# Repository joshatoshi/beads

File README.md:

# Mutable Instruments Beads Pedalboard Skiff, Stereo Audio/MIDI-to-CV Bridge & Autonomous Drift Workstation

A complete, fabrication-ready **low-profile guitar pedalboard skiff (`152.0 × 185.6 × 45.0 mm`, Bambu Lab X2D `PETG-HF`)** that houses an unmodified **Mutable Instruments Beads (`14 HP × 3U`)** Eurorack granular synthesizer directly on a standard **`9V–18V DC` center-negative guitar pedalboard**, pairing it with a **popless PhotoMOS + Omron relay stereo `1/4"` guitar interface**, **hardware `MIDI THRU` + `USB-C` MIDI**, and an **8-channel `-8.2V..+8.2V` `RP2040` Cubic Bezier "Drift" & calibrated `1V/Oct` CV workstation**.

---

## Visual Architecture & Mechanical Views

| North-Wall Pedalboard I/O | True Mechanical Y–Z Cross-Section |
|---|---|
|  |  |

| Exploded Multi-Board Architecture | Off-Board Wiring & Polarity Checklist |
|---|---|
|  |  |

---

## Key Engineering Highlights

1. **Multi-Stage Protected `9V–18V DC` Center-Negative → Ultra-Quiet `±12.0V` Eurorack Power (`plan/01`):**
   - Standard **`2.1 × 5.5 mm` Center-Negative** input (`Outer Sleeve = +9..18V`, `Center Pin = 0V GND`) via an all-insulated LCP panel DC jack (**Tensility `54-00401`**) into a **`33V 1.1A` resettable PTC (`SMD1812B110TF/33`, `C269134`)**, **`600W` bidirectional TVS (`SMBJ20CA`, `C19077576`)**, **`AO3401A` reverse-polarity P-MOSFET** with **`18V`-safe `9.1V` Zener gate clamp (`BZX84-C9V1`)**, and input LC Pi-filter (`BLM18PG121SN1D` `2A` ferrite).
   - **`TPS5430DDAR` (`+5.08V @ 500 kHz`, TI `SLVS632L` §7.2.3 RC-compensated: `PM = +87.3°` nominal / `+68.2°` derated, `GM = +20.5 / +15.3 dB`, `164.1 µF` output bank)** → **`TPS65131RGER` (`+14.65V / -14.56V @ 1.38 MHz` fixed-PWM, `PSP/PSN=GND`)** → linear **`LM317AG-TN3-R` (`+12.0V_EUR`)** & ESR-damped **`79M12(TP)` (`-12.0V_EUR`)** post-regulators + `2A` ferrite LC filters feeding the shrouded **`2×5` Eurorack IDC box header (`J_EURO_PWR`)** marked **`RED STRIPE / -12V (PINS 1-2)`**.
   - **`< 1 µA` Bidirectional `USB-C VBUS` ↔ `+5V_BUCK` Isolation, Glitch-Free USB 2.0 Suspend & `3.3V → 5V` Level Shifting:** `D_OR_PED` (`1N5819WS`) + `D_ESD_VP` (`1N4148W`) + `C100` (`100 nF`) reverse-isolated `SRV05-4` `ESD_VP` clamp + `PIN_VBUS_DET`-gated `RP2040` `1.5 kΩ` D+ pull-up (`< 3 nA` zero back-feed into powered-off hosts and immediate `< 16 mV` hot-unplug `VBUS_DET` drop with zero `SUSPENDED` `SE0` glitches!) + `I_off`-isolated **`SN74AHCT541PWR`** (`C50989`) SPI/CS level shifter with `+5V_BUCK` pull-ups (`R77..R80`), ensuring `MCP4822` `V_IH >= 3.56V` compliance during simultaneous `USB-C` + pedal DC or USB-only UF2 bench flashing.

2. **Stereo `1/4"` Guitar ↔ Eurorack Gain Staging & Boutique Popless PhotoMOS True Bypass (`plan/02`):**
   - `4×` North-edge PCB-mounted **Neutrik `NMJ4HCD2`** `1/4"` jacks (`OUT R`, `OUT L/Mono`, `IN R` passively normalled from `IN L/Mono` via `TN`; output `TN` pins strictly isolated — **zero flying audio wires!**).
   - **`1 MΩ` `TL072CDT` JFET Stereo Guitar Preamp** (`+18.0 dB` at `12 o'clock` on dual-gang `IN TRIM` → `SEND L / SEND R` Thonkiconn) paired with **`100 kΩ` `NE5532DR` + `TL072CDT` Stereo Return** (`-18.0 dB` at `12 o'clock` on dual-gang `OUT TRIM` ← `RET L / RET R` Thonkiconn) = **`0.0 dB` end-to-end unity gain and `0°` non-inverting phase**.
   - **Clickless / Popless Relay True Bypass (`15.0 ms` Window + `250 ms` POR Blanking):** Combines `2× Omron G6K-2F-Y-TR DC5` gold-clad DPDT relays (`fail-safe passive copper bypass when unpowered`) with **`2× Toshiba TLP172AM` (`SOP-4`, `3.75 kV` optical isolation, `0 pC` charge injection) PhotoMOS shunt mutes** (`47.3 dB` mute attenuation, `< 1.6 mV` bounce transient), `8× 2.2 MΩ` zero-DC bleed resistors, soft-slewed coil/LED drive, and **EQD Flexi-Switch auto-momentary** (`short tap < 350 ms` toggles; `hold >= 350 ms` momentarily engages Beads while held).
   - **Overvoltage-Proof Guitar Peak & Pluck Detector:** `+3.30V`-powered **`MCP6002T-I/SN`** + `BAV99` clamp (`<= 2.79V` even under `12 Vpk` fault surges) feeding `RP2040 ADC0`.

3. **8× Universal `-8.2V..+8.2V` Bipolar CV / Calibrated `1V/Oct` / Gate Outputs + Hardware `MIDI THRU` (`plan/02`, `plan/05`):**
   - `4× MCP4822-E/SN` (`12-bit` Dual SPI DACs, internal `2.048V` ref, `0xFFFF` delta-gated SPI) + `CJ431`/`OP07CDR` `+2.495V` precision offset reference + `4× TL072CDT` bipolar drivers + `1 kΩ` protection resistors → `8×` `WQP-PJ398SM` Thonkiconn jacks (`CV 1..CV 8`).
   - Top-mounted `3.5 mm` TRS `MIDI IN` with right-angle **C&K `JS202011AQN` `MIDI TYPE A / B`** crossover switch → **`H11L1M` (`DIP-6`)** optocoupler → **`74HC14D` zero-latency hardware `MIDI THRU`** (`3.5 mm` TRS Type A) + `RP2040 UART0_RX` merged seamlessly with **`USB-C` MIDI**.
   - Per-channel **Autonomous `C¹` Cubic Bezier Random Drift**, free/clock-synced **256-pt LFOs** (`Sine`, `Tri`, `Ramp Up/Down` for `TIME` scrubbing, `Square`, `Slewed S&H`), **Euclidean `(Steps, Hits)` Triggers**, **9-Octave LUT-Calibrated `1V/Oct` Pitch CV**, **MIDI Gate/Trig/Clock-Div/CC**, **Guitar Envelope/Pluck**, and **FS2 `FREEZE` / `SEED` Tap-Tempo** — viewed on a **`0.96"` `128×64` `SSD1306` OLED oscilloscope** and stored in **dual-slot A/B `CRC32` + `write_seq` QSPI Flash (`32` presets)**.

4. **Cost-Optimized 3-Board 2-Layer JLCPCB Partitioning & Bambu Lab X2D `PETG-HF` Stepped Enclosure (`plan/03`, `plan/04`):**
   - **`main_board` (`142.0 × 146.6 mm`, 2-layer `1.6 mm` FR4):** Single-sided Top-Side JLCPCB SMT PCBA (`77` unique verified LCSC parts: **`54` Basic, `7` Preferred, `16` Extended**, `314` SMD placements, `0` THT in CPL, **`92.46%` single largest connected `B.Cu` ground island** with `0` un-stitched islands, `0.80 × 1.60 mm` `SJ1-3523N` plated slots, `0.500 mm` min NPTH edge web + `0.70 mm` `SJ1-3523N` collar relief notches, `203` PCB nets, `ERC = 0/0`, `DRC = 0` errors / `0` warnings, `unconnected = 0`).
   - **`ui_mezzanine` (`68.0 × 108.0 mm`, 2-layer `1.6 mm` FR4, `$0` PCBA fee):** Pure user-hand-soldered THT carrier (`12×` Thonkiconn, `SSD1306` w/ reversible `JP_OLED_PWR` & `8.13 mm <= 8.50 mm` low-profile `DW-04-07-T-S-200` stack, `EC11E15244G1` 15 PPR bushingless, `BACK`, `2×` vertical dual-gang `10 kΩ` trim pots `Alpha RD902F-40-15R1-B10K-00D`, `PEAK` LED, `B.Cu`-mounted `0.0000 mm` XY-matched `2×8` BTB sockets, `21/21` local `${KIPRJMOD}` 3D STEP links).
   - **`faceplate_14hp` (`70.80 × 128.50 mm`, 2-layer `1.6 mm` Matte-Black FR4, `$0` PCBA fee):** Sits on the `-1.60 mm` Left 3U rail shelf alongside Mutable Instruments Beads on the `-2.00 mm` Right 3U rail shelf — **both panels dead-flush at `Z = 0.00 mm`** above a `-12.00 mm` stepped front stomp apron (`92.0 mm` footswitch spacing) reinforced by `4×` full-height internal stomp pillars and `18×` `M3` brass heat-set inserts (**`0.000 mm³` pairwise `OCP BRepAlgoAPI_Common` collision across all `427` un-grouped solids + `0.000 mm³` `15`-pose × `331`-part rigid-body insertion sweep**).

---

## Repository Structure

```text
├── PLAN.md                           # Master specification index
├── README.md                         # Project overview, flashing & verification guide
├── hardware_contract.json            # Single-source-of-truth spatial, PCB & GPIO contract
├── plan/                             # Authoritative 00..05 engineering specifications
├── hardware/
│   ├── main_board/                   # KiCad 9 2-layer Main Floor PCB + hierarchical schematics
│   ├── ui_mezzanine/                 # KiCad 9 2-layer 14HP THT Mezzanine PCB
│   ├── faceplate_14hp/               # KiCad 9 14HP Matte-Black FR4 Eurorack Panel
│   ├── beads_custom.kicad_sym        # Project-local ERC-typed custom schematic symbols
│   ├── beads_custom.pretty/          # Project-local custom footprints (${KIPRJMOD}-portable)
│   ├── beads_custom.3dshapes/        # Local parametric 3D STEP component models
│   └── spice/verify_analog.py        # Netlist-derived 8-gate ngspice verification suite
├── manufacturing/
│   ├── main_board/                   # Gerbers, Drills, Schematic PDF, JLCPCB SMT BOM & CPL
│   ├── ui_mezzanine/                 # Gerbers, Drills, Schematic PDF & THT BOM
│   ├── faceplate_14hp/               # Gerbers, Drills & Schematic PDF (Matte Black FR4)
│   └── HAND_SOLDER_AND_BOM.md        # Complete JLCPCB order settings, DigiKey/Thonk BOM & build guide
├── firmware/
│   ├── Makefile & CMakeLists.txt     # Bare-metal ARM UF2 build + Pico SDK CMake + Host unit tests
│   ├── include/ & src/               # Dual-core RP2040 C11 engine, Bezier/LFO/1V-Oct, OLED, Presets
│   ├── target/                       # RP2040 XIP boot2, linker script & silicon register HAL
│   ├── tests/test_beads_firmware.c   # 12 deterministic host silicon-mock assert() test suites
│   └── build/beads_bridge.uf2        # Ready-to-flash RP2040 UF2 firmware image (0xE48BFF56)
├── cad/
│   ├── build_enclosure.py            # Parametric Build123d enclosure, 427-solid assembly & studio renderer
│   ├── verify_3d_collisions.py       # 427-solid pairwise + 331-part kinematic OCP BRepAlgoAPI_Common 0.000 mm³ gate
│   └── exports/                      # Print-ready STLs, STEPs, Studio PNGs & Wiring Diagram
└── scripts/
    ├── generate_3d_shapes.py         # Deterministic STEP builder for hardware/beads_custom.3dshapes
    ├── layout_boards.py              # Deterministic KiCad 9 board placement & outline generator
    ├── route_boards.py               # Specctra DSN + bounded Freerouting + fresh-process zone filler
    ├── verify_pcb_gates.py           # Gate 1 KiCad 9 ERC/DRC/Pour/BTB/Paste/Keepout verifier
    ├── export_manufacturing.py       # Gate 2 Gerber/BOM/CPL exporter & jlcpcb_parts.db verifier
    └── run_all_checks.sh             # Master 5-gate end-to-end verification suite
```

---

## Headerless USB-C UF2 Firmware Flashing (`Zero SWD Pins Required`)

1. **First-Time Factory Bring-Up:**
   - Plug a `USB-C` cable from your computer into the North-wall `USB-C` port (with or without `9–18V` pedal power connected — `< 1 µA` isolated!).
   - A fresh `RP2040` automatically enumerates as **`RPI-RP2`** USB Mass Storage. Copy `firmware/build/beads_bridge.uf2` directly onto the `RPI-RP2` drive.
2. **In-Case Field Updates (No Disassembly Needed):**
   - **Via Front-Panel OLED:** Press `BACK` from the Scope view to enter **`SYSTEM MENU`**, scroll to **`USB FW UPDATE`**, and click the encoder — the skiff reboots immediately into `RPI-RP2` UF2 mode.
   - **Via `1200-baud` USB-CDC Touch:** Run `picotool load -f firmware/build/beads_bridge.uf2` (or open/close the virtual serial port at `1200 bps`).
   - **Hardware Fallback:** Hold onboard SMD **`BOOTSEL` (`SW_BOOT`)** while plugging in `USB-C`.

---

## Bambu Lab X2D `PETG-HF` 3D Printing Guide

- **Print Files:** `cad/exports/beads_enclosure_shell.stl` (`152.0 × 185.6 × 45.0 mm`) and `cad/exports/beads_bottom_lid.stl` (`147.1 × 180.7 × 5.0 mm`).
- **Recommended Bambu Studio Settings (`Bambu Lab X2D`):**
  - **Nozzle 1 (Structural Body):** **Bambu `PETG-HF`** (Charcoal / Black), `0.4 mm` hardened steel nozzle, `0.20 mm` layer height, **`4` wall loops**, `5` top / `5` bottom shell layers, **`25%` Gyroid infill**.
  - **Nozzle 2 (Dedicated Support Interface):** **`Support for PLA/PETG`** (or soluble breakaway interface), `0 mm` top Z-distance, `2` interface layers under the 3U Eurorack rail lips and stepped front stomp apron ceiling for glass-flat overhang surfaces.
  - **Orientation:** Place `beads_enclosure_shell.stl` **flat upright (`Z = -45.0 mm` outer skirt on textured PEI plate)** and `beads_bottom_lid.stl` **outer bottom face (`Z = -45.0 mm`) down on textured PEI plate**.
- Full hand-soldering, `18× M3` heat-set insert installation, `JP_OLED_PWR` jumper selection, and step-by-step wiring instructions are in **[`manufacturing/HAND_SOLDER_AND_BOM.md`](manufacturing/HAND_SOLDER_AND_BOM.md)**.

---

## Reproducing All 5 Verification Gates End-to-End

```bash
bash scripts/run_all_checks.sh
```

`scripts/run_all_checks.sh` executes all 5 mandatory engineering gates from scratch and exits `0`:
1. **Gate 1 (`scripts/verify_pcb_gates.py`):** KiCad 9 `ERC = 0/0`, `DRC = 0` errors / `0` warnings, `unconnected = 0` across all 3 boards, `${KIPRJMOD}` portability + `21/21` `ui_mezzanine` & `SW_MIDI_AB` local STEPs, `92.46%` single largest connected `B.Cu` GND island (`>= 88%`, `0` un-stitched islands), `>= 0.50 mm` bulk power trunks, `0.500 mm` (`>= 0.35 mm`) min NPTH edge web, `0.600 mm` (`>= 0.50 mm`, `L >= 2*W`) min plated-slot DFM across PCB & `PTH.drl` (`0.80 × 1.60 mm` `SJ1-3523N` slots), `F.Cu↔B.Cu` `0.0000 mm` `J_BTB_*` XY congruence, segmented `F.Paste` (`0` via-in-paste), `3.32 mm` `MH*` non-GND keepout, and full-sheet `A2`/`A4` schematic bounds + synced `.net` netlists.
2. **Gate 2 (`scripts/export_manufacturing.py`):** Exports Gerbers, PTH/NPTH drills, schematic PDFs, BOMs, and EasyEDA Pin-1/centroid-verified CPL (`100%` matched against `jlcpcb_parts.db`, `0` zero-stock, `0` THT in CPL).
3. **Gate 3 (`hardware/spice/verify_analog.py`):** Netlist-derived `8`-gate `ngspice` batch verification of `9–18V` RPP + `9.1V` gate clamp, `< 1 µA` bidirectional USB isolation including `D_ESD_VP` (`1N4148W`) + `C100` reverse-isolated `U_USB_ESD` (`SRV05-4`) + `PIN_VBUS_DET` D+ pull-up gating + glitch-free `< 16 mV` hot-unplug `VBUS_DET` drop (with `PULLUP_EN=1` held continuously) + USB-only `+3V3_DIG`/ESD hot-plug latch test, `> 45 dB` `TLP172AM` popless mute (`< 2 mV` bounce spike), `0.0 dB` `12-o'clock` stereo unity & `0°` phase, `±8.16V` CV span (`CJ431` `R143` stabilized), `<= 3.30V` `MCP6002` mono/stereo ADC clamp, and `TPS5430DDAR` (`TI SLVS632L` Eq. 15 + §7.2.3) AC Bode loop stability (`PM = +87.3°` nominal / `+68.2°` derated `>= 45°`, `GM = +20.5 / +15.3 dB >= 10 dB`).
4. **Gate 4 (`firmware/Makefile`):** `arm-none-eabi-gcc -Wall -Wextra -Werror -fstack-usage` producing `firmware/build/beads_bridge.uf2` (`0xE48BFF56`, `16 MB` `W25Q128JVSIQ` flash target), `0` 64-bit/float/soft-div helpers in Core 0 RT, `120 B` max stack frame, `EP_CTRL_INTERRUPT_PER_BUFFER` + glitch-free `PIN_VBUS_DET` dynamic `PULLUP_EN`/`VBUS_DETECT` gating (`0` suspend `SE0` glitches) + `WC` `SUSPENDED` clear on `DEV_SOF` + `< 500 µs` continuous Core 1 USB polling (`511 µs << 2.0 ms` `SET_ADDRESS` latency, `<= 16 B` chunked OLED I2C, EP0-active deferral) + `BUFF_STATUS`-before-`SETUP_REC` verified in ELF & both HALs, and `12/12` host silicon-mock `assert()` test suites.
5. **Gate 5 (`cad/verify_3d_collisions.py`):** `Build123d` + `OCP BRepAlgoAPI_Common` **`0.000000 mm³` pairwise intersection** across all `427` un-grouped solids (`90,951` pairs, including all `306` SMD bodies & `ISO 7380-1` `k=1.65 mm` `MH101..103` bolts), **`0.000000 mm³` rigid-body `main_board` insertion sweep** (`15` poses × `331` soldered parts at `+0.35°` South-down pitch), `1.00 mm` `SW_MIDI_AB` alcove rim + debossed North-wall `B ◄ ► A`, `0.35 mm` (`<= 0.50 mm`) `J_USB` reach (`2.69 mm` North-wall web), `8.13 mm` (`<= 8.50 mm`) `SSD1306` stack, and `+8.40 mm` / `+13.40 mm` (`>= 8.00 mm`) shaft protrusions.

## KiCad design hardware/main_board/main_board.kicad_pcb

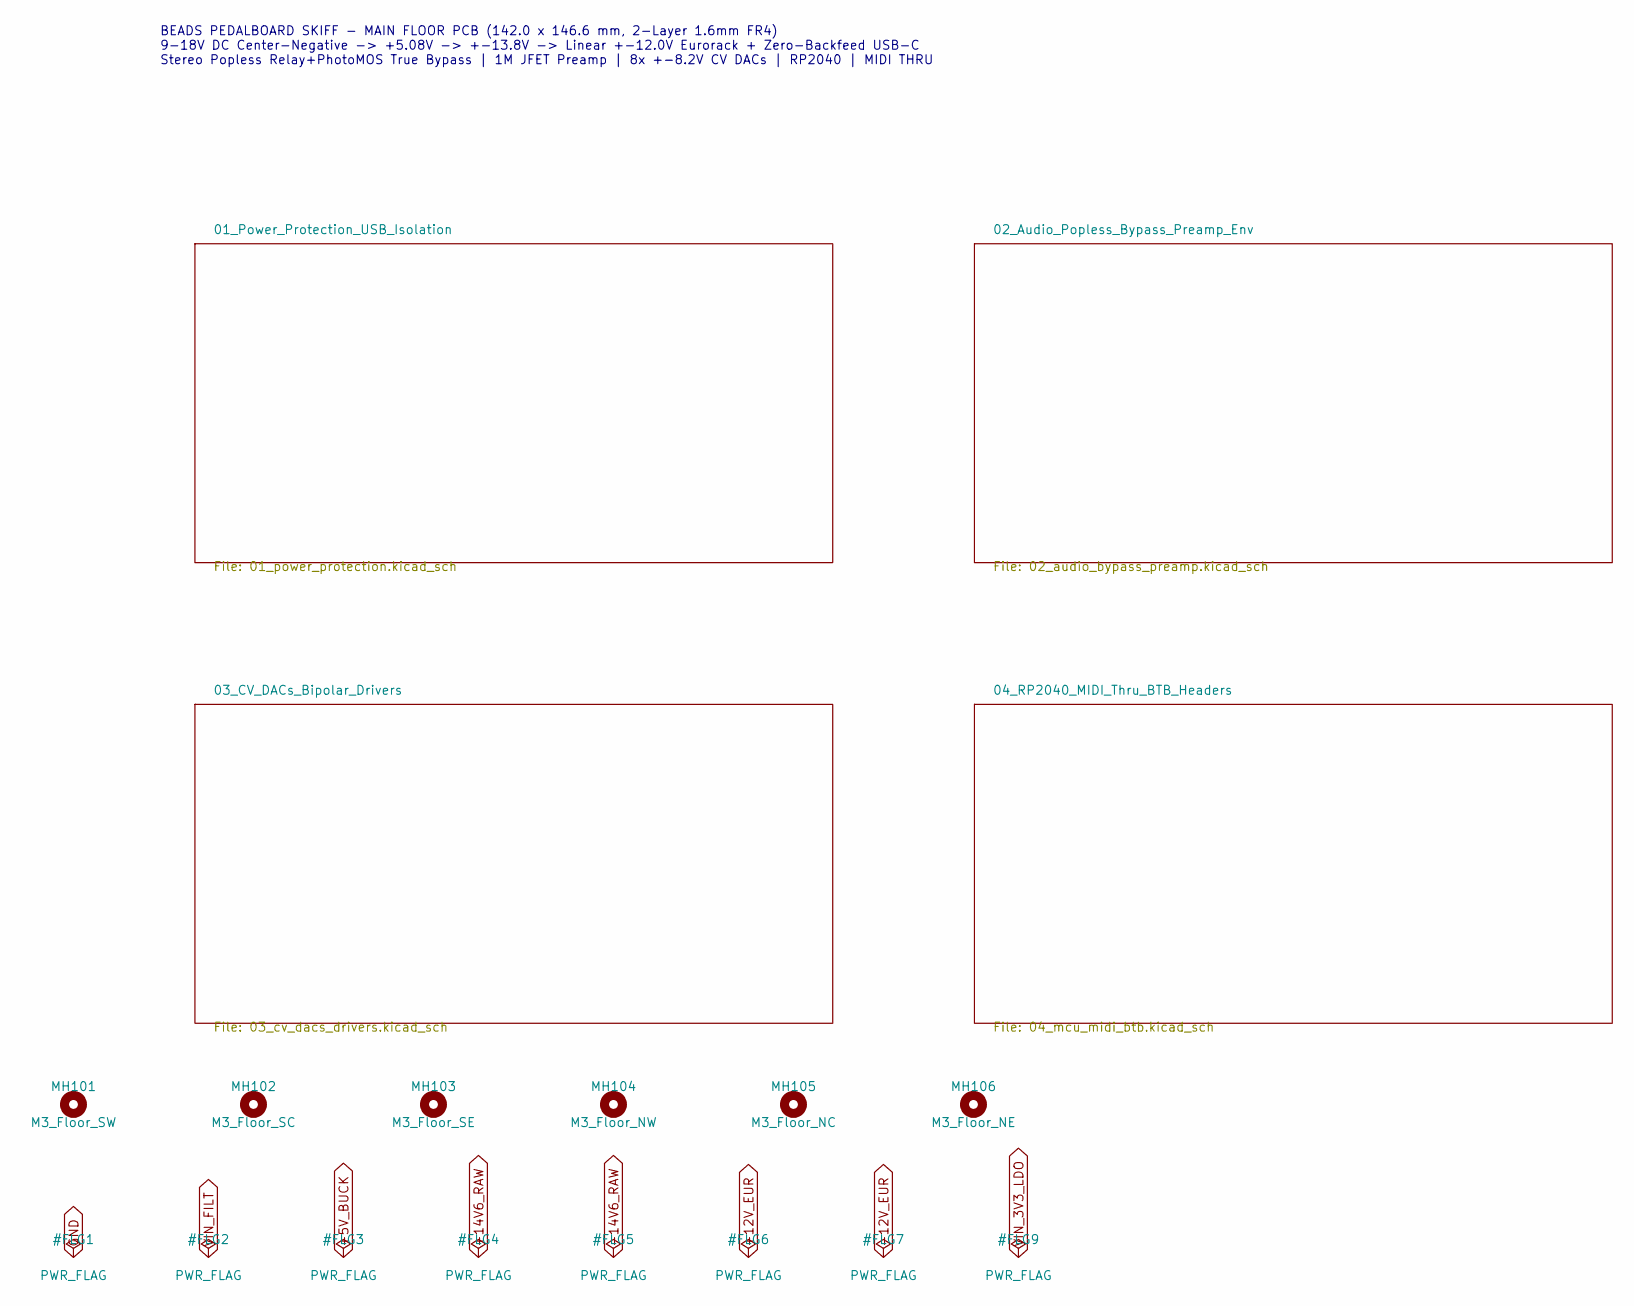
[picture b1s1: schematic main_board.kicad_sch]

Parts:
MH101: M3_Floor_SW; MountingHole_3.2mm_M3
MH102: M3_Floor_SC; MountingHole_3.2mm_M3
MH103: M3_Floor_SE; MountingHole_3.2mm_M3
MH104: M3_Floor_NW; MountingHole_3.2mm_M3
MH105: M3_Floor_NC; MountingHole_3.2mm_M3
MH106: M3_Floor_NE; MountingHole_3.2mm_M3

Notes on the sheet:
BEADS PEDALBOARD SKIFF - MAIN FLOOR PCB (142.0 x 146.6 mm, 2-Layer 1.6mm FR4) 9-18V DC Center-Negative -> +5.08V -> +-13.8V -> Linear +-12.0V Eurorack + Zero-Backfeed USB-C Stereo Popless Relay+PhotoMOS True Bypass | 1M JFET Preamp | 8x +-8.2V CV DACs | RP2040 | MIDI THRU

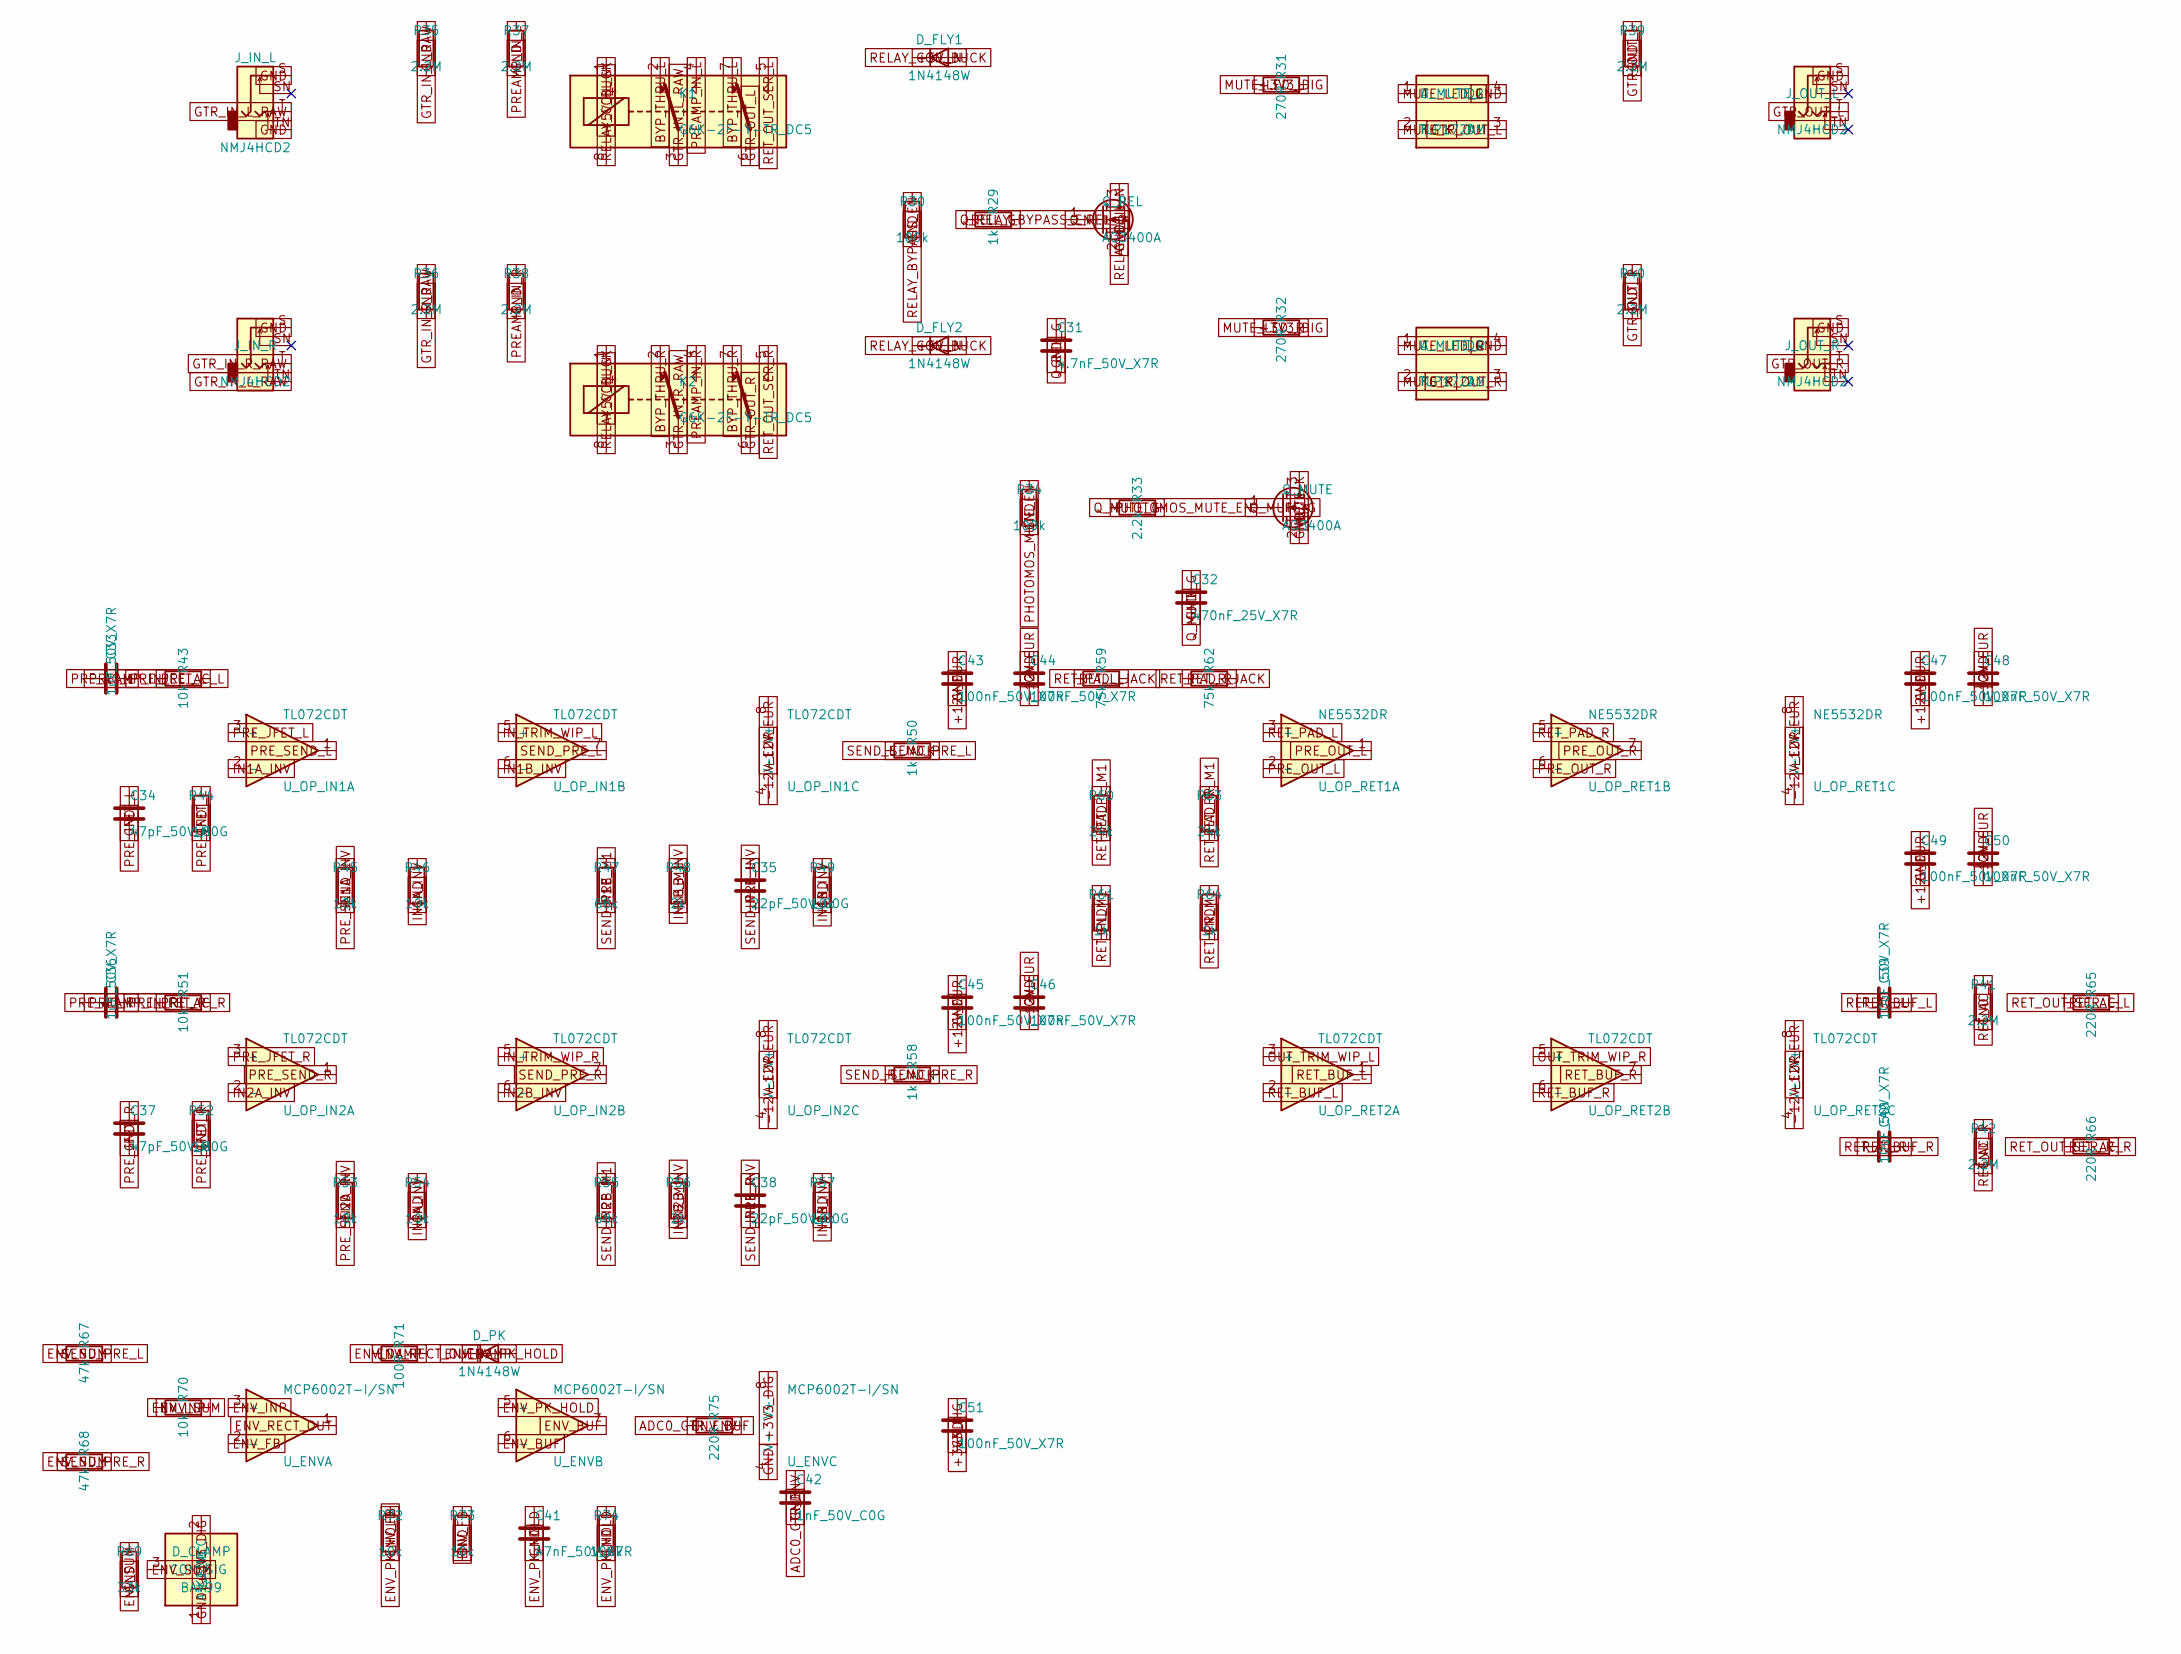
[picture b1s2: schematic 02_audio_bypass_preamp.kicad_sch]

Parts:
C31: 4.7nF_50V_X7R; C_0603_1608Metric
C32: 470nF_25V_X7R; C_0603_1608Metric
C33, C36: 1uF_50V_X7R; C_0805_2012Metric
C34, C37: 47pF_50V_C0G; C_0603_1608Metric
C35, C38: 22pF_50V_C0G; C_0603_1608Metric
C39, C40: 10uF_50V_X7R; C_1206_3216Metric
C41: 47nF_50V_X7R; C_0603_1608Metric
C42: 1nF_50V_C0G; C_0603_1608Metric
C43, C44, C45, C46, C47, C48, C49, C50, C51: 100nF_50V_X7R; C_0603_1608Metric
D_CLAMP: BAV99; SOT-23
D_FLY1, D_FLY2: 1N4148W; D_SOD-123
D_PK: 1N4148W; D_SOD-123
J_IN_L: NMJ4HCD2; Jack_6.35mm_Neutrik_NMJ4HCD2_TightCrtYd
J_IN_R: NMJ4HCD2; Jack_6.35mm_Neutrik_NMJ4HCD2_TightCrtYd
J_OUT_L: NMJ4HCD2; Jack_6.35mm_Neutrik_NMJ4HCD2_TightCrtYd
J_OUT_R: NMJ4HCD2; Jack_6.35mm_Neutrik_NMJ4HCD2_TightCrtYd
K1, K2: G6K-2F-Y-TR_DC5; Relay_DPDT_Omron_G6K-2F-Y
Q_MUTE: AO3400A; SOT-23
Q_REL: AO3400A; SOT-23
R29, R50, R58, R61, R64: 1k; R_0603_1608Metric
R30, R34, R74: 100k; R_0603_1608Metric
R31, R32: 270R; R_0603_1608Metric
R33: 2.2k; R_0603_1608Metric
R35, R36, R37, R38, R39, R40, R41, R42: 2.2M; R_0603_1608Metric
R43, R45, R46, R49, R51, R53, R54, R57, R70, R72, R73: 10k; R_0603_1608Metric
R44, R52: 1M; R_0603_1608Metric
R47, R55: 68k; R_0603_1608Metric
R48, R56: 2k; R_0603_1608Metric
R59, R62: 75k; R_0603_1608Metric
R60, R63: 24k; R_0603_1608Metric
R65, R66, R75: 220R; R_0603_1608Metric
R67, R68: 47k; R_0603_1608Metric
R69: 33k; R_0603_1608Metric
R71: 100R; R_0603_1608Metric
U_ENV: MCP6002T-I/SN; SOIC-8_3.9x4.9mm_P1.27mm
U_MUTE_L: TLP172AM; SOP-4_TLP172AM_P2.54mm
U_MUTE_R: TLP172AM; SOP-4_TLP172AM_P2.54mm
U_OP_IN1, U_OP_IN2: TL072CDT; SOIC-8_3.9x4.9mm_P1.27mm
U_OP_RET1: NE5532DR; SOIC-8_3.9x4.9mm_P1.27mm
U_OP_RET2: TL072CDT; SOIC-8_3.9x4.9mm_P1.27mm

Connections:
+3V3_DIG: C51.1, D_CLAMP.2 (K2_VCC), R31.1, R32.1, U_ENV.8 (V+); also elsewhere on the board
+5V_BUCK: D_FLY1.1 (K), D_FLY2.1 (K), K1.1, K2.1; also elsewhere on the board
+12V_EUR: C43.1, C45.1, C47.1, C49.1, U_OP_IN1.8 (V+), U_OP_IN2.8 (V+), U_OP_RET1.8 (V+), U_OP_RET2.8 (V+); also elsewhere on the board
-12V_EUR: C44.2, C46.2, C48.2, C50.2, U_OP_IN1.4 (V-), U_OP_IN2.4 (V-), U_OP_RET1.4 (V-), U_OP_RET2.4 (V-); also elsewhere on the board
ADC0_GTR_ENV: C42.1, R75.2; also elsewhere on the board
BYP_THRU_L: K1.2, K1.7
BYP_THRU_R: K2.2, K2.7
ENV_BUF: R75.1, U_ENV.6 (-), U_ENV.7
ENV_DAMP: D_PK.2 (A), R71.2
ENV_FB: R72.2, R73.1, U_ENV.2 (-)
ENV_INP: R70.2, U_ENV.3 (+)
ENV_PK_HOLD: C41.1, D_PK.1 (K), R72.1, R74.1, U_ENV.5 (+)
ENV_RECT_OUT: R71.1, U_ENV.1
ENV_SUM: D_CLAMP.3 (COM_SIG), R67.2, R68.2, R69.1, R70.1
GND: C31.2, C32.2, C34.2, C37.2, C41.2, C42.2, C43.2, C44.1, C45.2, C46.1, C47.2, C48.1, C49.2, C50.1, C51.2, D_CLAMP.1 (A1_GND), J_IN_L.S, J_IN_L.TN, J_IN_R.S, J_OUT_L.S, J_OUT_R.S, Q_MUTE.2 (S), Q_REL.2 (S), R30.2, R34.2, R35.2, R36.2, R37.2, R38.2, R39.2, R40.2, R41.2, R42.2, R44.2, R46.2, R49.2, R52.2, R54.2, R57.2, R61.2, R64.2, R69.2, R73.2, R74.2, U_ENV.4 (V-), U_MUTE_L.4 (D2), U_MUTE_R.4 (D2); also elsewhere on the board
GTR_IN_L_RAW: J_IN_L.T, J_IN_R.TN, K1.3, R35.1
GTR_IN_R_RAW: J_IN_R.T, K2.3, R36.1
GTR_OUT_L: J_OUT_L.T, K1.6, R39.1, U_MUTE_L.3 (D1)
GTR_OUT_R: J_OUT_R.T, K2.6, R40.1, U_MUTE_R.3 (D1)
IN1A_INV: R45.2, R46.1, U_OP_IN1.2 (-)
IN1B_INV: C35.2, R48.2, R49.1, U_OP_IN1.6 (-)
IN1B_M1: R47.2, R48.1
IN2A_INV: R53.2, R54.1, U_OP_IN2.2 (-)
IN2B_INV: C38.2, R56.2, R57.1, U_OP_IN2.6 (-)
IN2B_M1: R55.2, R56.1
IN_TRIM_WIP_L: U_OP_IN1.5 (+); also elsewhere on the board
IN_TRIM_WIP_R: U_OP_IN2.5 (+); also elsewhere on the board
MUTE_K: Q_MUTE.3 (D), U_MUTE_L.2 (K), U_MUTE_R.2 (K)
MUTE_LED_L: R31.2, U_MUTE_L.1 (A)
MUTE_LED_R: R32.2, U_MUTE_R.1 (A)
OUT_TRIM_WIP_L: U_OP_RET2.3 (+); also elsewhere on the board
OUT_TRIM_WIP_R: U_OP_RET2.5 (+); also elsewhere on the board
PHOTOMOS_MUTE_EN: R33.1, R34.1; also elsewhere on the board
PREAMP_IN_L: C33.1, K1.4, R37.1
PREAMP_IN_R: C36.1, K2.4, R38.1
PRE_AC_L: C33.2, R43.1
PRE_AC_R: C36.2, R51.1
PRE_JFET_L: C34.1, R43.2, R44.1, U_OP_IN1.3 (+)
PRE_JFET_R: C37.1, R51.2, R52.1, U_OP_IN2.3 (+)
PRE_OUT_L: U_OP_RET1.1, U_OP_RET1.2 (-); also elsewhere on the board
PRE_OUT_R: U_OP_RET1.6 (-), U_OP_RET1.7; also elsewhere on the board
PRE_SEND_L: R45.1, U_OP_IN1.1; also elsewhere on the board
PRE_SEND_R: R53.1, U_OP_IN2.1; also elsewhere on the board
Q_MUTE_G: C32.1, Q_MUTE.1 (G), R33.2
Q_REL_G: C31.1, Q_REL.1 (G), R29.2
RELAY_BYPASS_EN: R29.1, R30.1; also elsewhere on the board
RELAY_COIL_N: D_FLY1.2 (A), D_FLY2.2 (A), K1.8, K2.8, Q_REL.3 (D)
RET_AC_L: C39.2, R41.1, R65.1
RET_AC_R: C40.2, R42.1, R66.1
RET_BUF_L: C39.1, U_OP_RET2.1, U_OP_RET2.2 (-)
RET_BUF_R: C40.1, U_OP_RET2.6 (-), U_OP_RET2.7
RET_L_JACK: R59.1; also elsewhere on the board
RET_OUT_SER_L: K1.5, R65.2
RET_OUT_SER_R: K2.5, R66.2
RET_PAD_L: R59.2, R60.1, U_OP_RET1.3 (+)
RET_PAD_R: R62.2, R63.1, U_OP_RET1.5 (+)
RET_PL_M1: R60.2, R61.1
RET_PR_M1: R63.2, R64.1
RET_R_JACK: R62.1; also elsewhere on the board
SEND_L_JACK: R50.2; also elsewhere on the board
SEND_PRE_L: C35.1, R47.1, R50.1, R67.1, U_OP_IN1.7
SEND_PRE_R: C38.1, R55.1, R58.1, R68.1, U_OP_IN2.7
SEND_R_JACK: R58.2; also elsewhere on the board

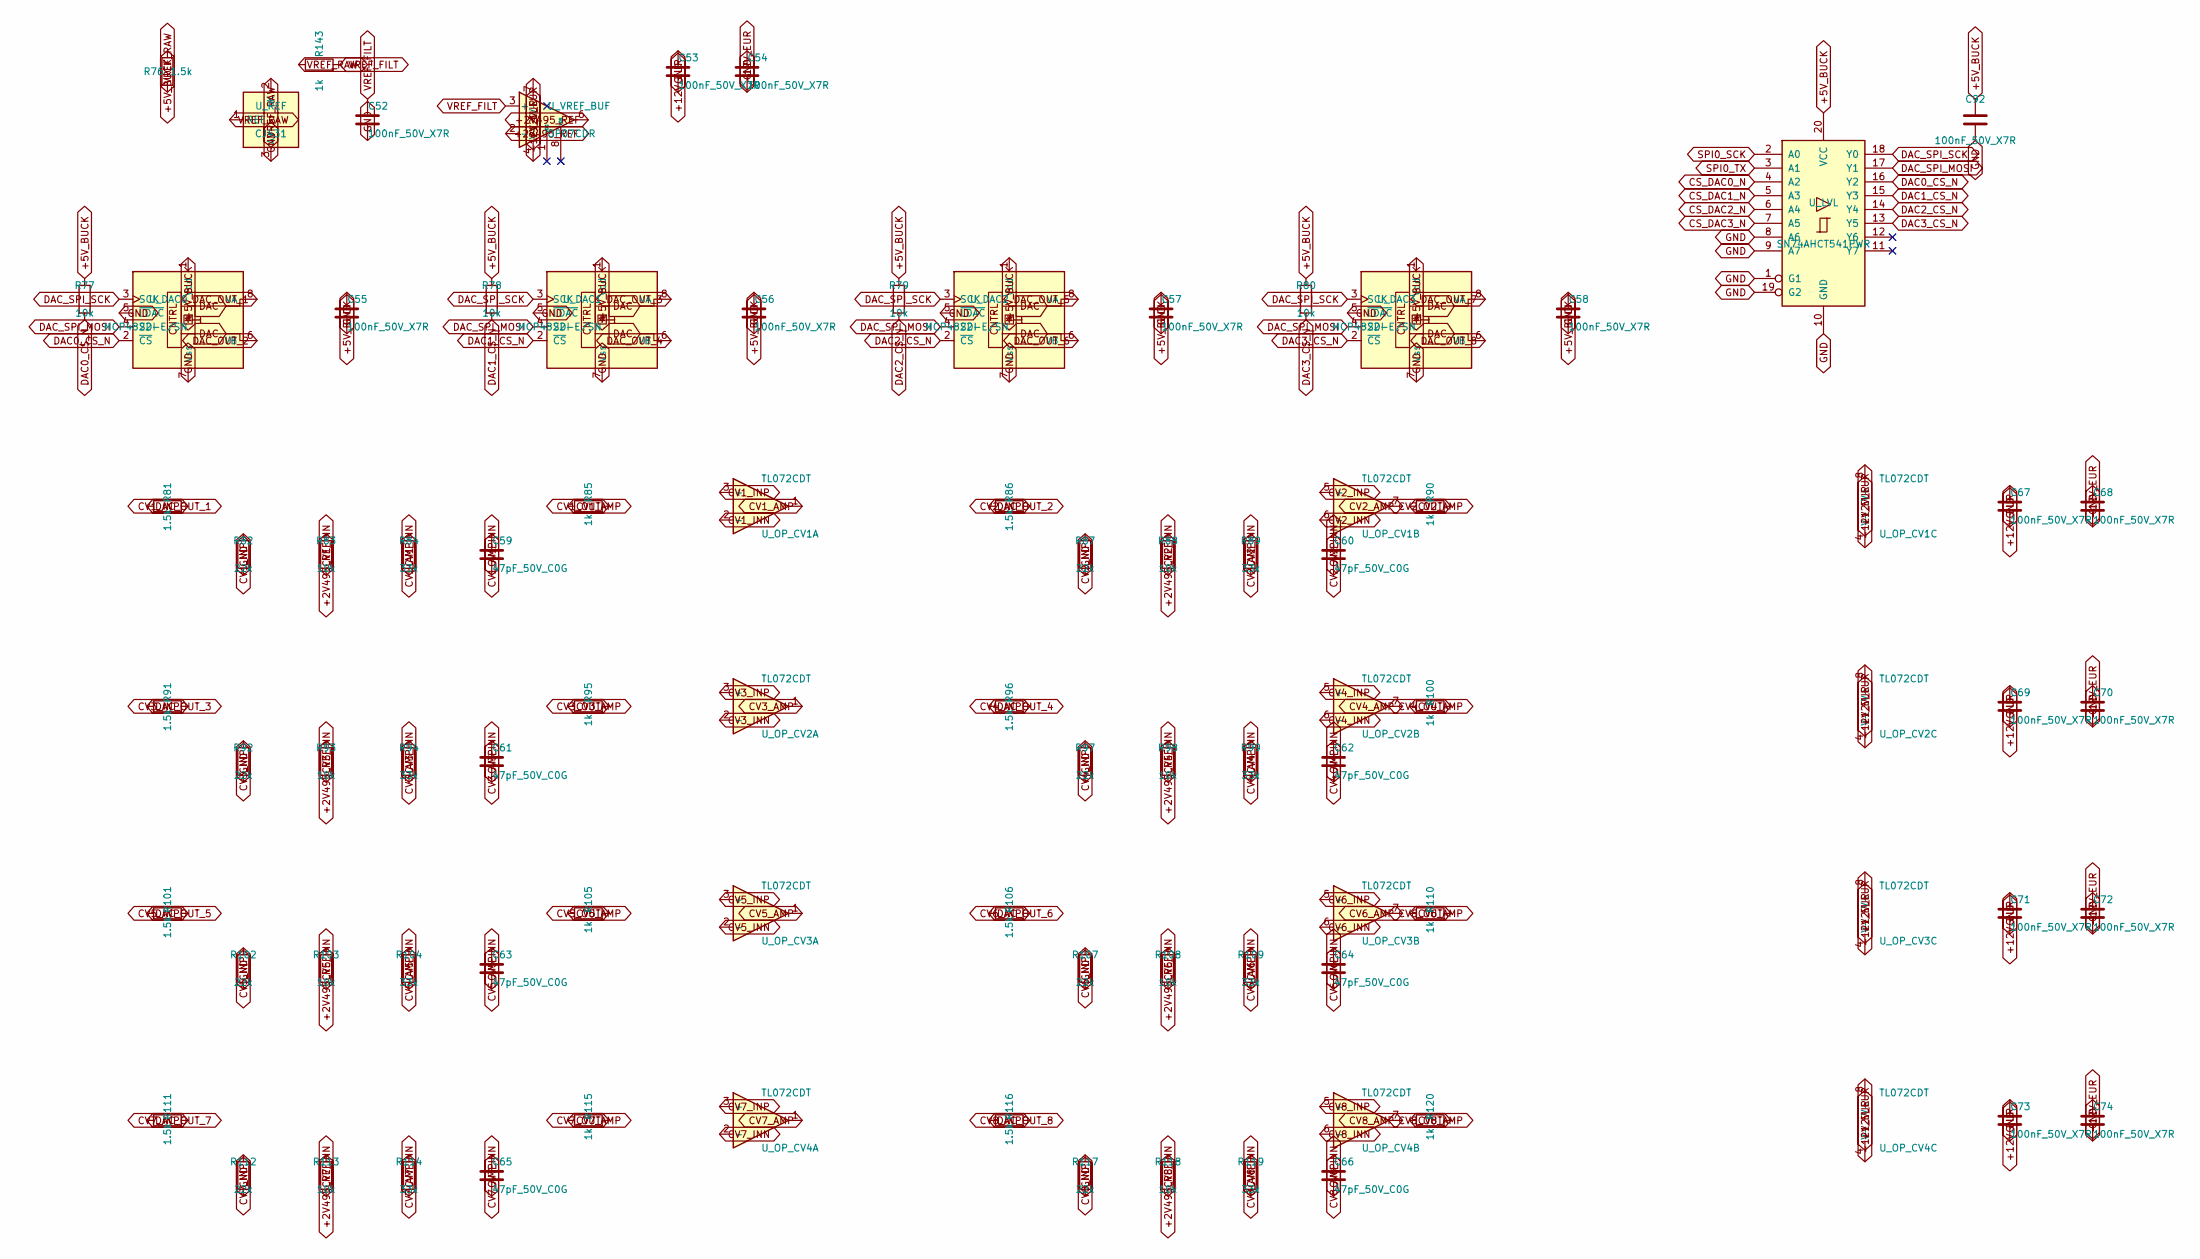
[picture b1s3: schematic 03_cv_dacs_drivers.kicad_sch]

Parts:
C52, C53, C54, C55, C56, C57, C58, C67, C68, C69, C70, C71, C72, C73, C74, C92: 100nF_50V_X7R; C_0603_1608Metric
C59, C60, C61, C62, C63, C64, C65, C66: 47pF_50V_C0G; C_0603_1608Metric
R76, R81, R86, R91, R96, R101, R106, R111, R116: 1.5k; R_0603_1608Metric
R77, R78, R79, R80, R83, R88, R93, R98, R103, R108, R113, R118: 10k; R_0603_1608Metric
R82, R87, R92, R97, R102, R107, R112, R117: 22k; R_0603_1608Metric
R84, R89, R94, R99, R104, R109, R114, R119: 33k; R_0603_1608Metric
R85, R90, R95, R100, R105, R110, R115, R120, R143: 1k; R_0603_1608Metric
U_DAC0, U_DAC1, U_DAC2, U_DAC3: MCP4822-E/SN; SOIC-8_3.9x4.9mm_P1.27mm
U_LVL: SN74AHCT541PWR; TSSOP-20_4.4x6.5mm_P0.65mm
U_OP_CV1, U_OP_CV2, U_OP_CV3, U_OP_CV4: TL072CDT; SOIC-8_3.9x4.9mm_P1.27mm
U_REF: CJ431; SOT-23
U_VREF_BUF: OP07CDR; SOIC-8_3.9x4.9mm_P1.27mm

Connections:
+2V495_REF: R83.1, R88.1, R93.1, R98.1, R103.1, R108.1, R113.1, R118.1, U_VREF_BUF.2 (-), U_VREF_BUF.6
+5V_BUCK: C55.1, C56.1, C57.1, C58.1, C92.1, R76.1, R77.1, R78.1, R79.1, R80.1, U_DAC0.1 (Vdd), U_DAC1.1 (Vdd), U_DAC2.1 (Vdd), U_DAC3.1 (Vdd), U_LVL.20 (VCC); also elsewhere on the board
+12V_EUR: C53.1, C67.1, C69.1, C71.1, C73.1, U_OP_CV1.8 (V+), U_OP_CV2.8 (V+), U_OP_CV3.8 (V+), U_OP_CV4.8 (V+), U_VREF_BUF.7 (V+); also elsewhere on the board
-12V_EUR: C54.2, C68.2, C70.2, C72.2, C74.2, U_OP_CV1.4 (V-), U_OP_CV2.4 (V-), U_OP_CV3.4 (V-), U_OP_CV4.4 (V-), U_VREF_BUF.4 (V-); also elsewhere on the board
CS_DAC0_N: U_LVL.4 (A2); also elsewhere on the board
CS_DAC1_N: U_LVL.5 (A3); also elsewhere on the board
CS_DAC2_N: U_LVL.6 (A4); also elsewhere on the board
CS_DAC3_N: U_LVL.7 (A5); also elsewhere on the board
CV1_AMP: C59.1, R84.1, R85.1, U_OP_CV1.1
CV1_INN: C59.2, R83.2, R84.2, U_OP_CV1.2 (-)
CV1_INP: R81.2, R82.1, U_OP_CV1.3 (+)
CV1_OUT: R85.2; also elsewhere on the board
CV2_AMP: C60.1, R89.1, R90.1, U_OP_CV1.7
CV2_INN: C60.2, R88.2, R89.2, U_OP_CV1.6 (-)
CV2_INP: R86.2, R87.1, U_OP_CV1.5 (+)
CV2_OUT: R90.2; also elsewhere on the board
CV3_AMP: C61.1, R94.1, R95.1, U_OP_CV2.1
CV3_INN: C61.2, R93.2, R94.2, U_OP_CV2.2 (-)
CV3_INP: R91.2, R92.1, U_OP_CV2.3 (+)
CV3_OUT: R95.2; also elsewhere on the board
CV4_AMP: C62.1, R99.1, R100.1, U_OP_CV2.7
CV4_INN: C62.2, R98.2, R99.2, U_OP_CV2.6 (-)
CV4_INP: R96.2, R97.1, U_OP_CV2.5 (+)
CV4_OUT: R100.2; also elsewhere on the board
CV5_AMP: C63.1, R104.1, R105.1, U_OP_CV3.1
CV5_INN: C63.2, R103.2, R104.2, U_OP_CV3.2 (-)
CV5_INP: R101.2, R102.1, U_OP_CV3.3 (+)
CV5_OUT: R105.2; also elsewhere on the board
CV6_AMP: C64.1, R109.1, R110.1, U_OP_CV3.7
CV6_INN: C64.2, R108.2, R109.2, U_OP_CV3.6 (-)
CV6_INP: R106.2, R107.1, U_OP_CV3.5 (+)
CV6_OUT: R110.2; also elsewhere on the board
CV7_AMP: C65.1, R114.1, R115.1, U_OP_CV4.1
CV7_INN: C65.2, R113.2, R114.2, U_OP_CV4.2 (-)
CV7_INP: R111.2, R112.1, U_OP_CV4.3 (+)
CV7_OUT: R115.2; also elsewhere on the board
CV8_AMP: C66.1, R119.1, R120.1, U_OP_CV4.7
CV8_INN: C66.2, R118.2, R119.2, U_OP_CV4.6 (-)
CV8_INP: R116.2, R117.1, U_OP_CV4.5 (+)
CV8_OUT: R120.2; also elsewhere on the board
DAC0_CS_N: R77.2, U_DAC0.2 (~CS), U_LVL.16 (Y2)
DAC1_CS_N: R78.2, U_DAC1.2 (~CS), U_LVL.15 (Y3)
DAC2_CS_N: R79.2, U_DAC2.2 (~CS), U_LVL.14 (Y4)
DAC3_CS_N: R80.2, U_DAC3.2 (~CS), U_LVL.13 (Y5)
DAC_OUT_1: R81.1, U_DAC0.8 (VA)
DAC_OUT_2: R86.1, U_DAC0.6 (VB)
DAC_OUT_3: R91.1, U_DAC1.8 (VA)
DAC_OUT_4: R96.1, U_DAC1.6 (VB)
DAC_OUT_5: R101.1, U_DAC2.8 (VA)
DAC_OUT_6: R106.1, U_DAC2.6 (VB)
DAC_OUT_7: R111.1, U_DAC3.8 (VA)
DAC_OUT_8: R116.1, U_DAC3.6 (VB)
DAC_SPI_MOSI: U_DAC0.4 (SDI), U_DAC1.4 (SDI), U_DAC2.4 (SDI), U_DAC3.4 (SDI), U_LVL.17 (Y1)
DAC_SPI_SCK: U_DAC0.3 (SCK), U_DAC1.3 (SCK), U_DAC2.3 (SCK), U_DAC3.3 (SCK), U_LVL.18 (Y0)
GND: C52.2, C53.2, C54.1, C55.2, C56.2, C57.2, C58.2, C67.2, C68.1, C69.2, C70.1, C71.2, C72.1, C73.2, C74.1, C92.2, R82.2, R87.2, R92.2, R97.2, R102.2, R107.2, R112.2, R117.2, U_DAC0.5 (~LDAC), U_DAC0.7 (Vss), U_DAC1.5 (~LDAC), U_DAC1.7 (Vss), U_DAC2.5 (~LDAC), U_DAC2.7 (Vss), U_DAC3.5 (~LDAC), U_DAC3.7 (Vss), U_LVL.1 (G1), U_LVL.8 (A6), U_LVL.9 (A7), U_LVL.10 (GND), U_LVL.19 (G2), U_REF.3 (A); also elsewhere on the board
SPI0_SCK: U_LVL.2 (A0); also elsewhere on the board
SPI0_TX: U_LVL.3 (A1); also elsewhere on the board
VREF_FILT: C52.1, R143.2, U_VREF_BUF.3 (+)
VREF_RAW: R76.2, R143.1, U_REF.1 (REF), U_REF.2 (K)
